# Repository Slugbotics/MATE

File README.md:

# MATE

## Git Standards
When making changes to the codebase, use feature branches. Tutorial can be found here https://medium.com/@stephencweiss/a-beginners-guide-to-feature-branch-workflows-with-git-7ae442df8e11

Donts:
- Do not push directly onto main, make a branch, make a pr, squash and merge.
- Do not let branches sit for too long, if they arent merged within a week or two, discard it and move on.
- Do not make changes to the build system without adding them to this README
- Do not add dependencies without adding them to requirements.txt

Dos:
- Use feature branches, make pull requests, squash and merge
- Keep branches to one feature at most
- Name the branch a one to two word description of the feature
- Use interactive rebase as the default merge strategy
- Format your code using clang-format (c++) or black (python)
- Commit messages should always be descriptive and with the following format:
    - "\<Imperative Verb> \<description of change>"

Python Standards:
- Use type declarations / hints for all functions
- write docstrings for non-obvious functions / methods
- always write docstrings for classes
- keep commenting minimal, if you code is not obvious, it is probably too complicated
- keep nesting minimal, if you can nest less, you probably should

## Installation
- Install virtualenv https://virtualenv.pypa.io/en/latest/installation.html
- `virtualenv env` to create the virtual environment
- Run `source env/bin/activate` to start the virtual environment
- Run `pip install -r requirements.txt` to install project dependencies
- Run `deactivate` when you are done

## Cameras
In order for the driver station GUI to properly access rover cameras:
- create a file in the root project directory called "cams.txt"
- find the device numbers of the cameras you want to use
- place the numbers in order separated by newline in "cams.txt"
    - example, say you wish to use cameras 6, 5, 8, 10
    - You would place "6\n5\n8\n10" into cams.txt

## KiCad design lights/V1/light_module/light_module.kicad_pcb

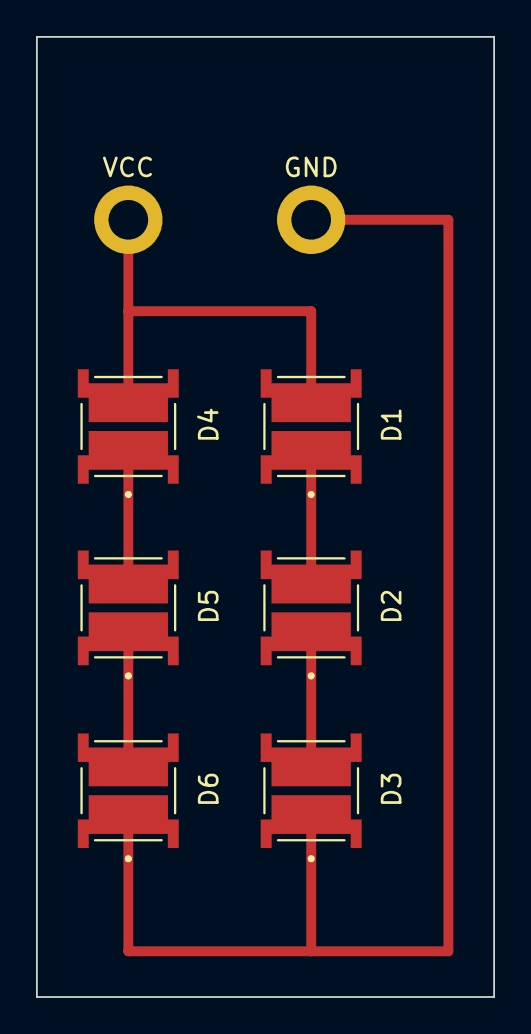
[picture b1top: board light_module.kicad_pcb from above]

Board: 2 copper layers, 25.4 x 53.3 mm, 8 parts (0 on the bottom side), 6 nets.

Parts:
D1, D2, D3, D4, D5, D6: MP-5050-250R-40-70; LED_MP-5050-250R-40-70
GND: GND; MountingHole_2.2mm_M2_DIN965_Pad
VCC: VCC; MountingHole_2.2mm_M2_DIN965_Pad

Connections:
unnamed: D1.A, D4.A, VCC.1
unnamed: D1.C, D2.A
unnamed: D2.C, D3.A
unnamed: D3.C, D6.C, GND.1
unnamed: D4.C, D5.A
unnamed: D5.C, D6.A

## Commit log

2023-10-08 Added example GUI code.
2023-10-16 Added basic input code.
2023-10-16 Add virtual environment
2023-10-16 Add directory for vision
2023-10-16 Real time object detection using yolov5
2023-10-23 Add gitignore
2023-10-23 Update requirements.txt with yolov5 requirements
2023-10-24 Added a basic polling input system.
2023-11-05 Object-detection with tkinter
2023-11-05 added socket file
2023-11-05 Add a test file for arduino code
2023-11-05 Move test.ino to the correct directory
2023-11-05 renamed socket.py
2023-11-05 updated network.py
2023-11-05 test server and client
2023-11-19 tcp to udp
2023-11-19 created client.py
2023-11-19 added server.py
2023-11-19 moved server.py into topside
2023-11-19 client.py complete
2023-11-19 finished server.py
2023-11-19 changed the name to add a 1
2023-11-19 fixed server
2023-11-19 testing connection between 2 terminals
2023-11-19 testing ip numbers
2023-11-19 changed server
2023-11-19 testing
2023-11-19 renamed client and server 1 and reverted them to tcp
2023-11-19 possible UDP
2023-11-19 Add test udp arduino code
2023-11-19 Move test.ino folder (god i hate arduino ide)
2023-11-20 UDP server to client
    - added code if we we want to send a message from the server to the client
    - added some comments
2023-11-20 Added V1 of lights
2023-12-03 Basic es control code, ethernet udp
    no checksum at the moment, fitted for 1 thruster
2023-12-03 Create arduino_control
2023-12-03 Create info
2023-12-03 added esc control code v1
    no checksum, controls 1 thruster
2023-12-03 Ethernet works.
2023-12-03 Input testing
2023-12-03 Two way communication.
2023-12-04 updated ip address of remote server
2024-01-15 added sample test harness
2024-01-20 Changed main code structure and test file
    >> created individual methods to setup ethernet udp connection and read/parse packet data
    >>modified to use strtol instead of atoi for better error handling
    >>updated test functions to refelct updated methods
2024-01-21 Basic communication test.
2024-01-21 Integrated input test with communication.
2024-01-21 Remove old files.
2024-01-21 Translated joystick inputs to motor values, returns scalars
2024-01-21 Merged branch 'input'
2024-01-21 Merged
2024-01-21 Convert motor values to correct range.
2024-01-25 Update Control.ino
    updated mac address to point to the correct shield unit on the mega
2024-01-25 Update Control.ino
    updated loop logic to prevent out of bounds
2024-01-27 Added arm file + random INO
2024-01-27 added controller file?
2024-01-27 init comit
2024-01-28 Added rotation and vertical translation control.
2024-01-28 Removed old networking test files.
2024-01-28 Changed motor value mapping and renamed some variables.
2024-01-28 updated control file
    fixed semicolon issue and undeclared thruster variable reference
2024-02-04 fixed buffer packet size
2024-02-17 Add pygal to requirements.txt
2024-02-17 Uploaded basic float code (Doesn't Work)
2024-02-17 Add the float data grapher
2024-02-18 PRESSURE SENSOR
    GIGA CHAD MOVEMENT
2024-02-25 Remove yolov5 obj det
2024-02-25 Add some logging into topside main
2024-02-25 added checksum and used a fstring for the packet
2024-02-25 Tested and fixed logging.
2024-02-25 Add basic camera gui
2024-02-25 Make the gui fullscreen
2024-02-25 Center the video input
2024-02-25 Remove old object detection, add some status bars to the gui
2024-02-25 Attempt to center the text element
2024-02-25 Move some tf files around, remove tkinter from object_detect
2024-02-25 Run the GUI inside of main
2024-02-25 Change version of pysimplegui
2024-02-25 Integrate gui with main
2024-03-04 PRESSURE SENSOR FILES TEST
2024-03-04 BNO055_IMU FILES TEST
2024-04-07 integrated pressure sensor and imu
    using bytes instead of strings, removed conversion block
2024-04-09 Move graph.py into proper directory
2024-04-09 Update the float grapher to use datetime objects and convert pressure
2024-04-09 Add pressure to depth conversion
2024-04-09 Orangized Float Folder to Topside and Float Code
2024-04-11 write data to file
2024-04-11 display graph on gui
2024-04-12 gets time
2024-04-12 added the float test data created to the topside folder generated by float
2024-04-14 timeworks
2024-04-14 added skeleton arm files
2024-04-18 wrote up things to do in README.md 2/16
2024-04-18 jonathan istg dont remove this
2024-04-18 Jonathan, do not touch. Arduino tests implemented
2024-04-18 fixed servo test to be a .ino
2024-04-18 AAAAAAAAAAA
2024-04-18 kill me
2024-04-18 WORKING SERVO TEST
2024-04-18 jonathan dont remove this. take out commas from packet
2024-04-18 jonathan dont remove. minor changes to arm test
2024-04-18 fixed var names
2024-04-18 Remove garbage obj det and remove space from armduino test dir
2024-04-18 Remove old armduino test
2024-04-18 I removed it
2024-04-20 Added table generation
2024-04-21 Send packets as byte array instead of str
2024-04-22 Add a nonworking test of the 6 camera setup
2024-04-22 Uncomment packet send and change button config
2024-04-22 Fixed Armduino folders
2024-04-23 send files
2024-04-26 updated stuff
2024-04-26 more usable
2024-04-26 rtc call test
2024-04-26 rtc call test2
2024-04-28 Working rtc calls
    Sends string down, and time when corresponding buttons are pressed. Can receive text file for data from what ever device that will be acting as the server.
2024-04-29 byte packet arduino changes
2024-04-29 VERY BROKEN: split the camera to a seperate window
2024-04-29 Added wireless ap stuff
2024-04-30 Threads are supported if you dont write dogshit code
2024-05-01 rtc calls
2024-05-05 changes packet structure to include 4 individual servo bytes with values
2024-05-05 Added tcp server to send file on pico w side
2024-05-10 pushing changes to button macros
2024-05-12 Updated the pico code
2024-05-13 General meeting changes
2024-05-17 Added support for continuous working and ignoring EINADDRUSE and ETIMEOUT issues
2024-05-17 uses byte reading method to receive file
2024-05-19 update code
2024-05-19 adjusted rtc
2024-05-19 finished v1 of float pico code
2024-05-21 float working and done
2024-05-22 Update videocapture backend to use vidgear
2024-05-22 fixed ESC.cpp
2024-05-22 fixed input and main
2024-05-22 Remove rover log from tracking
2024-05-22 Add camera switching in gui
2024-05-26 Remove project tasks from README, use issues instead
2024-05-26 Remove .vscode from tracking
    - users should customize their own environment
2024-05-26 Remove merge conflict headers from BNO055_IMU.h
2024-05-26 Fix broken ESC.h
    - When resolving merge conflicts, I accidentally pulled a url with html
    instead of the file directly
2024-05-26 Add an explanation for cams.txt in readme
2024-05-26 Remove cams.txt from tracking
2024-05-26 Remove unused dependencies from requirements.txt
2024-05-26 Arm2 (#42)
    * jonathan istg dont remove this
    * wrote up things to do in README.md 2/16
    * Merge main into mate_arm
    * Merge main into mate_arm
    * Merge main.py into mate_arm
    * Merge main into mate_arm
2024-06-02 deleted light files
2024-06-02 Update BNO055_IMU.cpp
    fixed typo.
2024-06-02 More readme changes
2024-06-02 Add some git standards
2024-06-02 Removal of Pressure Sensor from ROV Arduino code
2024-06-02 commented out imu items, finished getting rid of pressure sensor from rov
2024-06-02 added flush feature to attempt to fix mem leak
2024-06-02 fixed send packet issue
